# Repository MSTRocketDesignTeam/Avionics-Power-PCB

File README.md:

# Avionics-Power-PCB
KiCAD PCB files of rocket board designed to provide power and battery management functionalities

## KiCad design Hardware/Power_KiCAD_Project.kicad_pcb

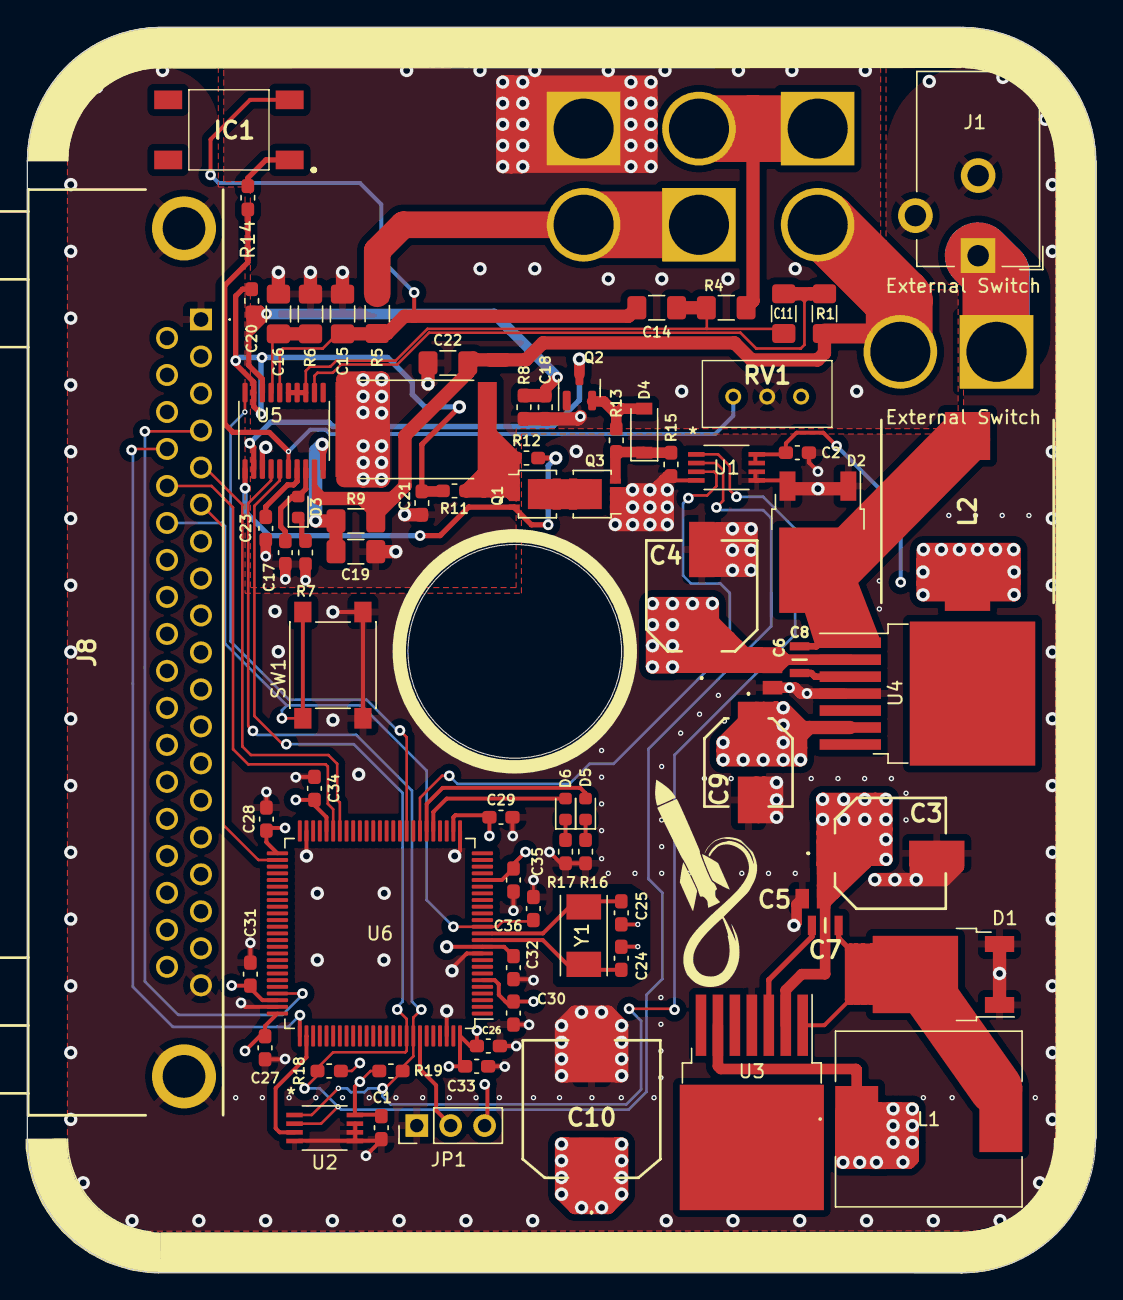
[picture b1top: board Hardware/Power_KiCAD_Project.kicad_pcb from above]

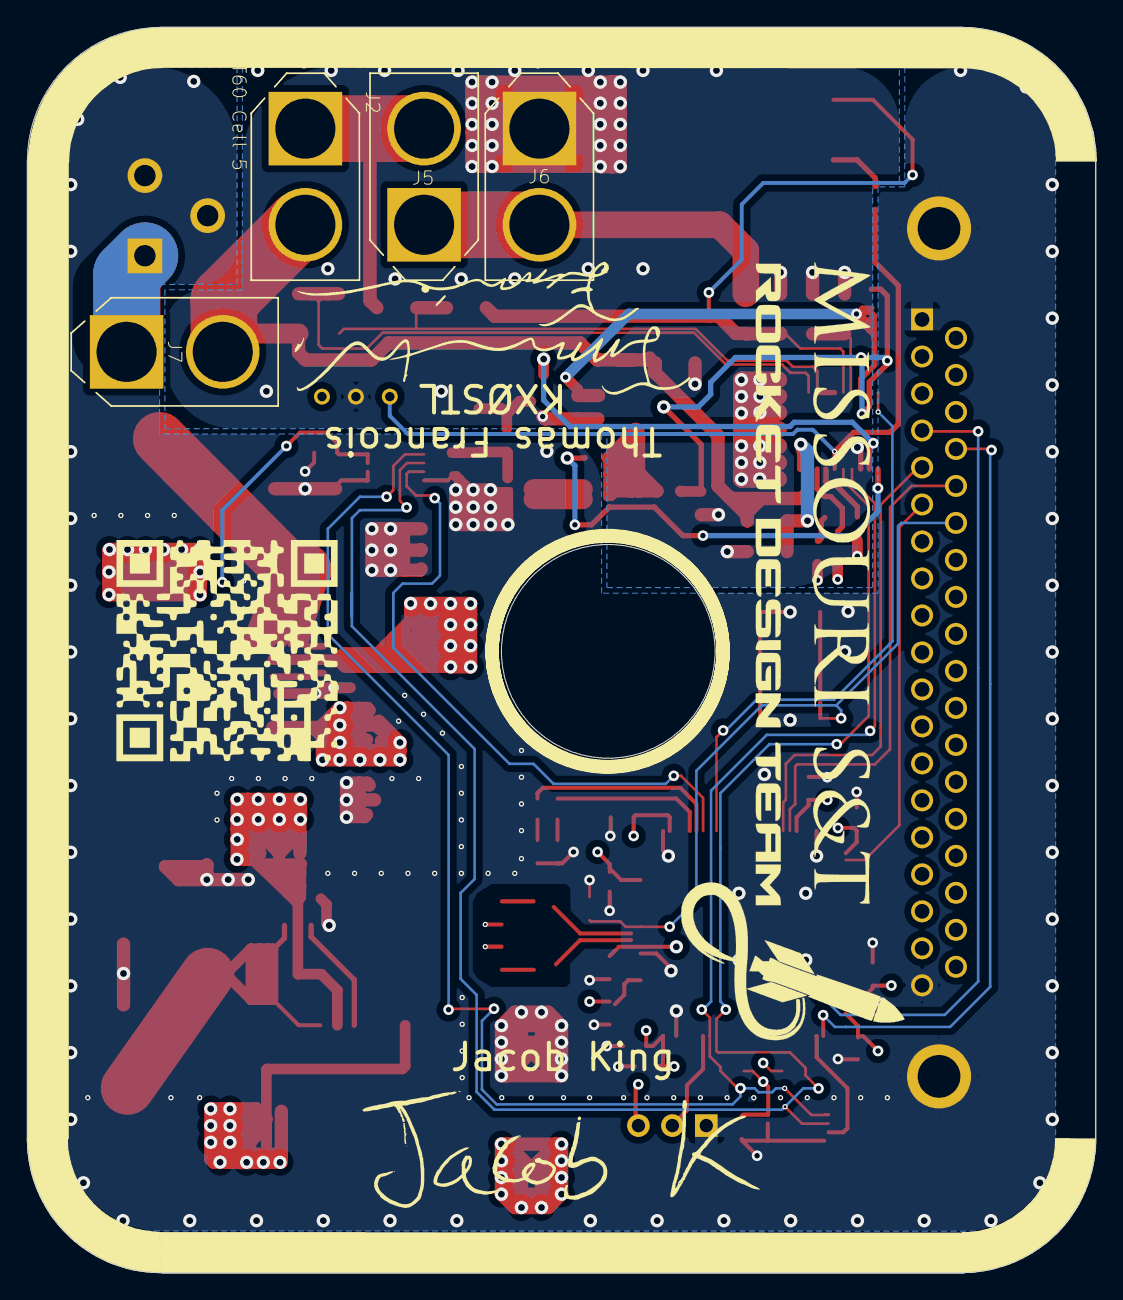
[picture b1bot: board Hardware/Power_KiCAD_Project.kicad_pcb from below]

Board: 4 copper layers, 80.0 x 93.2 mm, 79 parts (4 on the bottom side), 48 nets.

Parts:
C1, C2, C27, C28, C29, C30, C31, C32, C33, C34, C35, C36: 100nF; C_0603_1608Metric_Pad1.08x0.95mm_HandSolder
C3, C4: 35SVPF82M; 16SVPT560M
C5, C6: C0805C104M5RACTU; CAPC2012X88N
C7, C8: CGA4C2C0G1H103J060AA; CAPC2012X75N
C9: 6SVPC330M; 16SVF180M
C10: 16SVP330M; 16SVF1000M
C11, C14, C15, C16, C22: 1μF; C_1206_3216Metric_Pad1.42x1.75mm_HandSolder
C17: 4.7μF; C_0603_1608Metric_Pad1.08x0.95mm_HandSolder
C18, C20, C21: 0.1μF; R_0603_1608Metric_Pad1.05x0.95mm_HandSolder
C19: 10μF; C_1206_3216Metric_Pad1.42x1.75mm_HandSolder
C23: 1μF; C_0603_1608Metric_Pad1.08x0.95mm_HandSolder
C24, C25: 30pF; C_0603_1608Metric_Pad1.08x0.95mm_HandSolder
C26: 1uF; C_0603_1608Metric_Pad1.08x0.95mm_HandSolder
D1, D2: SBRD10200TR; TO-252-2
D3: LED; LED_0603_1608Metric
D4: 1N4148W-7-F; D_SOD-123
D5: GREEN; LED_0603_1608Metric
D6: RED; LED_0603_1608Metric
IC1: TL3301NF260QG
J1: Barrel_Jack_MountingPin; BarrelJack_CUI_PJ-102AH_Horizontal
J2: XT60 Cell 5; AMASS_XT60-M
J5: XT60 Cell 2; AMASS_XT60-M
J6: XT60 Cell 1; AMASS_XT60-M
J7: XT60 To External Switch; AMASS_XT60-M
J8: L717SDC37P1ACH4F
JP1: Debug Jumper; PinHeader_1x03_P2.54mm_Vertical
L1: IHLP5050FDER150M5A
L2: SRP1270-8R2M; INDPM137129X700N
Q1, Q3: PSMN2R6-40YS; LFPAK33
Q2: BSS84PH6327XTSA2; SOT-23
R1, R4, R5, R6, R9: 100Ω; R_1206_3216Metric_Pad1.42x1.75mm_HandSolder
R7, R16, R17: 1k5Ω; R_0603_1608Metric_Pad1.05x0.95mm_HandSolder
R8, R11: 100Ω; R_0603_1608Metric_Pad1.05x0.95mm_HandSolder
R10: CSS4527FT5L00
R12, R13, R15: 1MΩ; R_0603_1608Metric_Pad1.05x0.95mm_HandSolder
R14: 10kΩ; R_0603_1608Metric_Pad1.05x0.95mm_HandSolder
R18, R19: 4.7k; R_0603_1608Metric_Pad1.05x0.95mm_HandSolder
RV1: 10Ω to 2.2MΩ; T93YA5K10
SW1: MCU Reset; SW_SPST_PTS645
U1, U2: MIC184YMM-TR
U3: LM2678SX-5.0/NOPB; TO-263-7_TabPin8
U4: LM2678SX-3.3/NOPB; TO-263-7_TabPin8
U5: BQ76920PW; TSSOP-20_4.4x6.5mm_P0.65mm
U6: STM32L562VET; LQFP-100_14x14mm_P0.5mm
Y1: 32MHz; XTAL_ABM7-32.000MHZ-D2Y-T

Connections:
+3V3: C1.1, C2.1, C9.1, C26.1, C27.1, C28.1, C29.1, C30.1, C31.1, C32.1, C33.1, C34.1, C35.1, J8.2, J8.18, JP1.3 (B), L2.2, R18.2, R19.2, U1.7 (A0), U1.8 (VDD), U2.8 (VDD), U4.6 (FB), U6.6 (VBAT), U6.11 (VDD), U6.21 (VDDA), U6.27 (VDD), U6.46 (VDDSMPS), U6.51 (VDD), U6.73 (VDDUSB), U6.75 (VDD), U6.100 (VDD)
+5V: C10.1, J8.20, J8.37, L1.1, U3.6 (FB)
/BATT_ALERT: U5.20 (ALERT), U6.34 (PB2)
/Buck_Converters/V_IN: C3.1, C4.1, C5.1, C6.1, J1.1, J7.1 (-), U3.2 (VIN), U4.2 (VIN)
/DSUB-37_Bus/Alert_Active: J8.6, U6.52 (PB13)
/DSUB-37_Bus/Alert_scl: J8.5, U6.44 (PB10)
/DSUB-37_Bus/Alert_sda: J8.24, U6.45 (PB11)
/DSUB-37_Bus/NRST: C36.1, J8.25, SW1.1, U6.14 (NRST)
/DSUB-37_Bus/SWCLK: J8.23, U6.76 (PA14)
/DSUB-37_Bus/SWDIO: J8.4, U6.72 (PA13)
/I2C_SCL: R18.1, U1.2 (CLK), U2.2 (CLK), U5.5 (SCL), U6.92 (PB6)
/I2C_SDA: R19.1, U1.1 (DATA), U2.1 (DATA), U5.4 (SDA), U6.93 (PB7)
/LiPo Pack Monitor/VC0: C16.2, R6.2, U5.17 (VC0)
/LiPo Pack Monitor/VC1: C14.2, C15.1, IC1.3, R5.2, U5.16 (VC1)
/LiPo Pack Monitor/VC2: C11.2, C14.1, R4.2, U5.13 (VC4), U5.14 (VC3), U5.15 (VC2)
/LiPo Pack Monitor/VC5: C11.1, R1.2, U5.12 (VC5)
/PACK_M1: J5.1 (-), J6.2 (+), R5.1
/PACK_M2: J2.1 (-), J5.2 (+), R4.1
/PACK_M5: C22.2, J2.2 (+), J7.2 (+), R1.1, R9.1, U5.9 (REGSRC)
/TEMP_ALERT_1: U1.3 (INT), U6.32 (PB0)
/TEMP_ALERT_2: U2.3 (INT), U6.77 (PA15)
GND: C1.2, C2.2, C3.2, C4.2, C5.2, C6.2, C9.2, C10.2, C24.2, C25.2, C26.2, C27.2, C28.2, C29.2, C30.2, C31.2, C32.2, C33.2, C34.2, C35.2, C36.2, D1.1, D1.3, D2.1, D2.3, J1.2, J1.3 (MountPin), J8.1, J8.19, J8.MH1, J8.MH2, JP1.1 (A), Q3.1 (S), Q3.2 (S), Q3.3 (S), R15.2, R16.2, R17.2, SW1.2, U1.4 (GND), U1.5 (A2/T1), U1.6 (A1), U2.4 (GND), U2.5 (A2/T1), U2.6 (A1), U2.7 (A0), U3.4 (GND), U4.4 (GND), U6.10 (VSS), U6.26 (VSS), U6.49 (VSS), U6.74 (VSS), U6.98 (VSS)
GNDREF: C15.2, C16.1, C17.1, C18.2, C19.1, C21.1, C22.1, C23.1, J6.1 (-), Q2.1 (G), R6.1, R7.2, R8.2, R10.1, RV1.2, U5.3 (VSS)
unnamed: C7.1, U3.3 (CB)
unnamed: C7.2, D1.2, L1.2, U3.1 (SWO)
unnamed: C8.1, U4.3 (CB)
unnamed: C8.2, D2.2, L2.1, U4.1 (SWO)
unnamed: C17.2, D3.2 (A), U5.8 (REGOUT)
unnamed: C18.1, C20.2, R8.1, U5.18 (SRP)
unnamed: C19.2, R9.2, U5.10 (BAT)
unnamed: C20.1, C21.2, R11.1, U5.19 (SRN)
unnamed: C23.2, U5.7 (CAP1)
unnamed: C24.1, U6.12 (PH0), Y1.1
unnamed: C25.1, U6.13 (PH1), Y1.2
unnamed: D3.1 (K), R7.1
unnamed: D4.1 (K), Q3.4 (G), R13.1, R15.1
unnamed: D4.2 (A), Q2.2 (S), R13.2
unnamed: D5.1 (K), R16.1
unnamed: D5.2 (A), U6.31 (PA7)
unnamed: D6.1 (K), R17.1
unnamed: D6.2 (A), U6.30 (PA6)
unnamed: IC1.1, R14.2
unnamed: JP1.2 (C), U6.94 (PH3)
unnamed: Q1.1 (S), Q1.2 (S), Q1.3 (S), R10.2, R11.2, R12.2
unnamed: Q1.4 (G), R12.1, U5.1 (DSG)
unnamed: Q1.5 (D), Q3.5 (D)
unnamed: Q2.3 (D), U5.2 (CHG)
unnamed: R14.1, RV1.1, U5.6 (TS1)

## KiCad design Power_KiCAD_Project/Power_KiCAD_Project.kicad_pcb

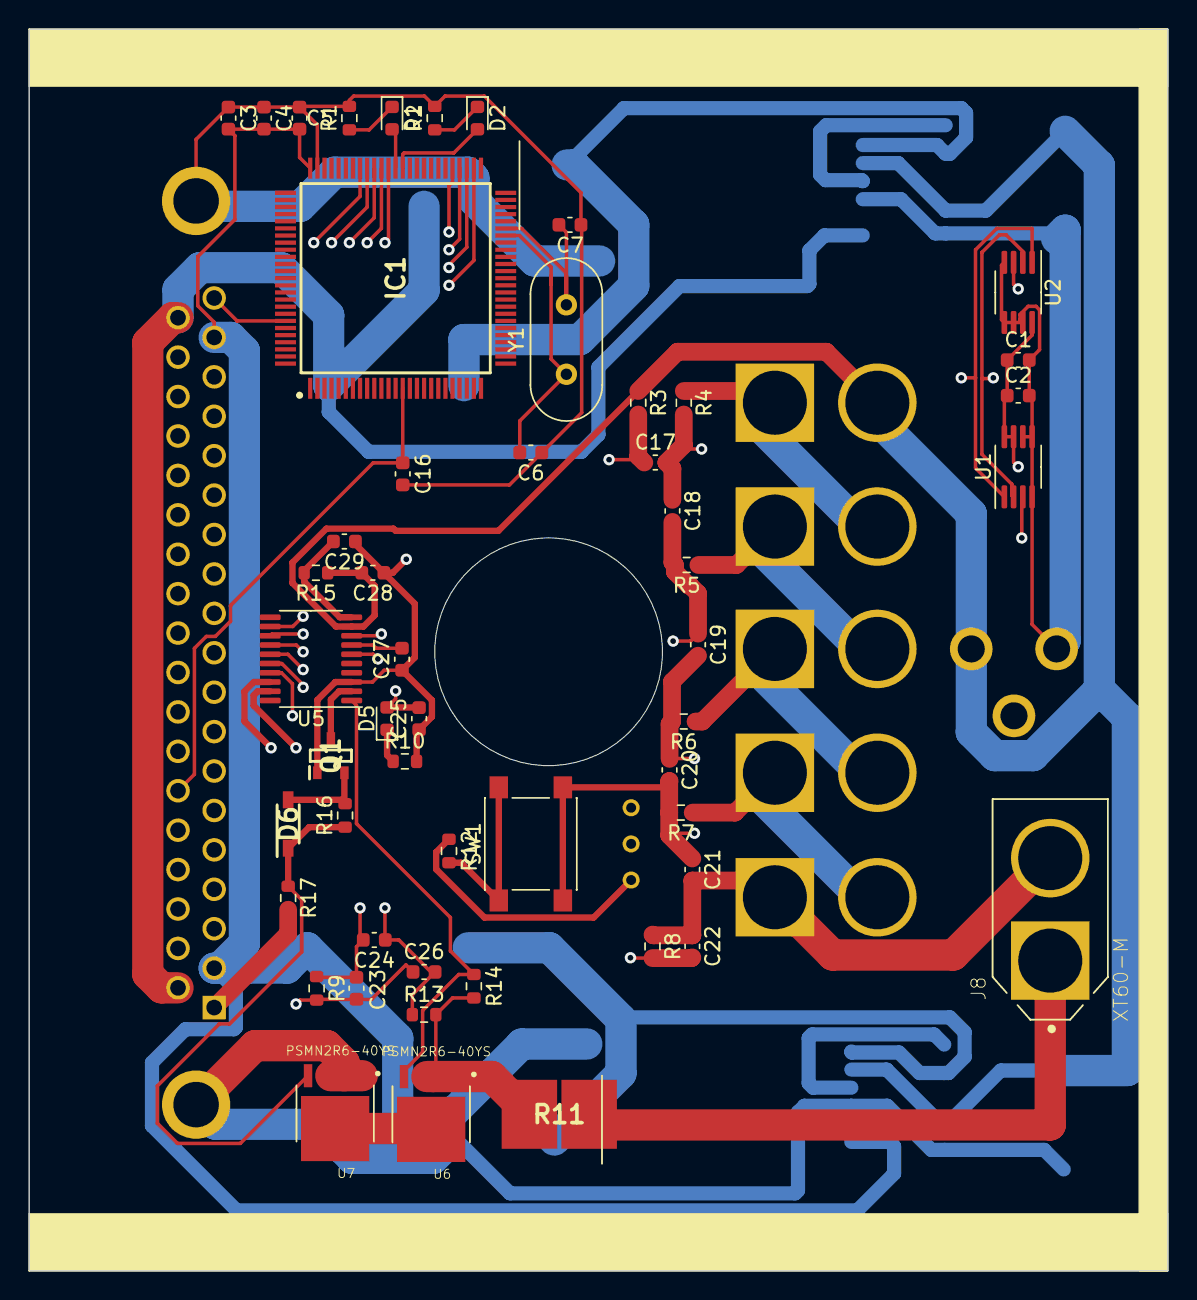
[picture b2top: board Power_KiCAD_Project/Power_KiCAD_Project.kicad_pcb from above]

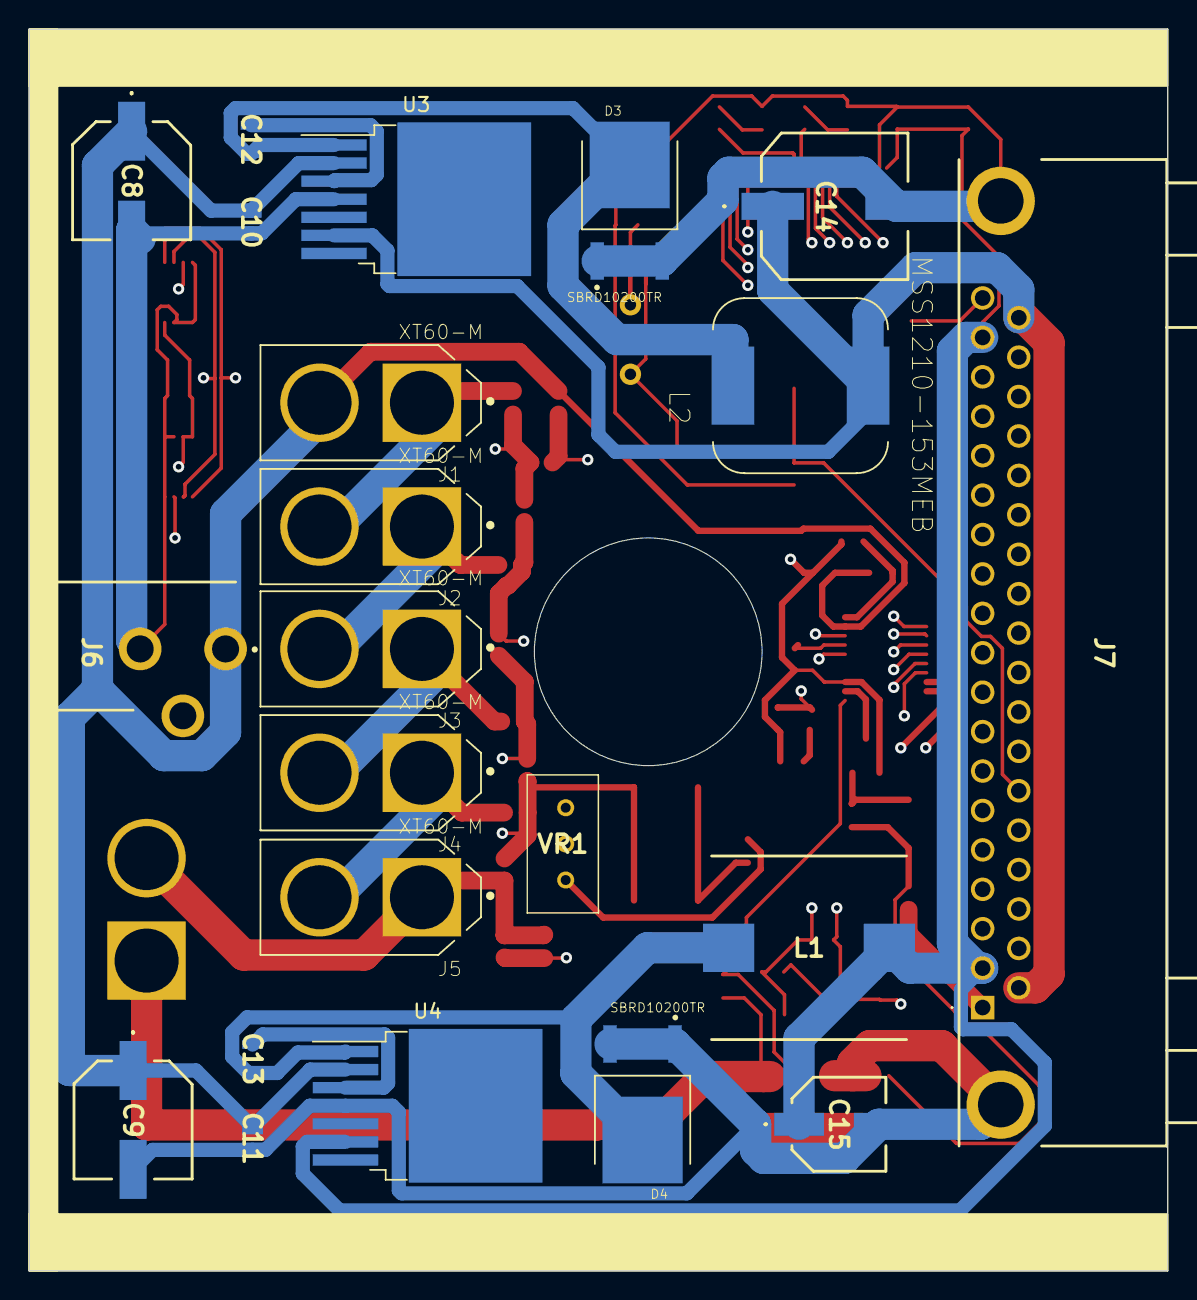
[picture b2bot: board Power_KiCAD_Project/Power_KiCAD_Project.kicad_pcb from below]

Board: 4 copper layers, 80.0 x 87.2 mm, 74 parts (22 on the bottom side), 49 nets.

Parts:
C1, C2, C4, C5, C16: 100nF; C_0603_1608Metric
C3: 1uF; C_0603_1608Metric
C6, C7: 30pF; C_0603_1608Metric
C8, C9: 35SVPF82M; 16SVPT560M
C10, C11: C0805C104M5RACTU; CAPC2012X88N
C12, C13: CGA4C2C0G1H103J060AA; CAPC2012X75N
C14: 16SVP330M; 16SVF1000M
C15: 6SVPC330M; 16SVF180M
C17, C18, C19, C20, C21, C22, C27, C28: 1μF; C_0603_1608Metric
C23, C24, C26: 0.1μF; C_0603_1608Metric
C25: 4.7μF; C_0603_1608Metric
C29: 10μF; C_0603_1608Metric
D1: GREEN; LED_0603_1608Metric
D2: RED; LED_0603_1608Metric
D3, D4: SBRD10200TR; DPAK228P1005X240-4N
D5: LED; LED_0603_1608Metric
D6: 1N4148W-7-F; SOD3716X145N
IC1: STM32L562VET6Q; QFP50P1600X1600X160-100N
J1, J2, J3, J4, J5, J8: XT60-M; AMASS_XT60-M
J6: PJ-102AH
J7: L717SDC37P1ACH4F
L1: SRP1270-8R2M; INDPM137129X700N
L2: MSS1210-153MEB; IND_MSS1210-153MEB
Q1: BSS84PH6327XTSA2; SOT95P240X110-3N
R1, R2, R10: 1k5Ω; R_0603_1608Metric
R3, R4, R5, R6, R7, R8, R9, R13, R15: 100Ω; R_0603_1608Metric
R11: WSHP28185L000FEA; RESC7146X175N
R12: 10kΩ; R_0603_1608Metric
R14, R16, R17: 1MΩ; R_0603_1608Metric
SW1: Reboot; SW_Push_1P1T_NO_6x6mm_H9.5mm
U1, U2: MCP9808_MSOP; MSOP-8_3x3mm_P0.65mm
U3: LM2678SX-5.0/NOPB; TO-263-7_TabPin8
U4: LM2678SX-3.3/NOPB; TO-263-7_TabPin8
U5: BQ76920PW; TSSOP-20_4.4x6.5mm_P0.65mm
U6, U7: PSMN2R6-40YS; TO127P600X120-5N
VR1: T93YA103KT20; T93YA5K10
Y1: Crystal; Crystal_HC49-4H_Vertical

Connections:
+3V3: C1.1, C2.1, C3.2, C4.2, C5.2, C15.1, IC1.75, J7.2, J7.18, L1.2, U1.7, U1.8, U2.8, U4.6
+5V: C14.1, J7.20, J7.37, L2.2, U3.6
/Alert_active: IC1.68, J7.6
/Alert_scl: IC1.66, J7.5
/Alert_sda: IC1.67, J7.24
/I2C_SCL: IC1.52, U1.2, U2.2
/I2C_SDA: IC1.53, U1.1, U2.1
/LiPo Pack Monitor/BAT: C29.2, R15.2, U5.10
/LiPo Pack Monitor/SRN: C24.1, C26.2, R13.1, U5.19
/LiPo Pack Monitor/SRP: C23.1, C24.2, R9.1, U5.18
/LiPo Pack Monitor/TS1: R12.1, U5.6, VR1.1
/LiPo Pack Monitor/VC0: C22.2, R8.2, U5.17
/LiPo Pack Monitor/VC1: C20.2, C21.1, R7.2, SW1.2, U5.16
/LiPo Pack Monitor/VC2: C19.2, C20.1, R6.2, U5.15
/LiPo Pack Monitor/VC3: C18.2, C19.1, R5.2, U5.14
/LiPo Pack Monitor/VC4: C17.2, C18.1, R4.2, U5.13
/LiPo Pack Monitor/VC5: C17.1, R3.2, U5.12
/NRST: C16.1, IC1.14, J7.25
/PACK_M1: J4.1, J5.2, R7.1
/PACK_M2: J3.1, J4.2, R6.1
/PACK_M3: J2.1, J3.2, R5.1
/PACK_M4: J1.1, J2.2, R4.1
/PACK_M5: C8.1, C9.1, C10.1, C11.1, C28.2, J1.2, J6.1, R3.1, R15.1, U3.2, U4.2, U5.9
/Pack-: C1.2, C2.2, C3.1, C4.1, C5.1, C6.1, C7.1, C8.2, C9.2, C10.2, C11.2, C14.2, C15.2, C16.2, D3.1, D3.3, D4.1, D4.3, IC1.74, IC1.94, J6.2, J7.1, J7.19, J7.MH1, J7.MH2, R1.2, R2.2, R17.2, U1.4, U1.5, U1.6, U2.4, U2.5, U2.6, U2.7, U3.4, U4.4, U7.1, U7.2, U7.3
/SWCLK: IC1.55, J7.23
/SWDIO: IC1.54, J7.4
/TEMP_ALERT_1: IC1.64, U1.3
/TEMP_ALERT_2: IC1.65, U2.3
GND: C21.2, C22.1, C23.2, C25.1, C26.1, C27.1, C28.1, C29.1, J5.1, J8.1, J8.2, Q1.1, R8.1, R9.2, R10.2, R11.1, U5.3, VR1.2, VR1.3
unnamed: C6.2, IC1.44, Y1.1
unnamed: C7.2, IC1.45, Y1.2
unnamed: C12.1, U3.3
unnamed: C12.2, D3.2, L2.1, U3.1
unnamed: C13.1, U4.3
unnamed: C13.2, D4.2, L1.1, U4.1
unnamed: C25.2, D5.2, U5.8
unnamed: C27.2, U5.7
unnamed: D1.1, R1.1
unnamed: D1.2, IC1.63
unnamed: D2.1, R2.1
unnamed: D2.2, IC1.62
unnamed: D5.1, R10.1
unnamed: D6.1, R16.1, R17.1, U7.4
unnamed: D6.2, Q1.2, R16.2
unnamed: Q1.3, U5.2
unnamed: R11.2, R13.2, R14.2, U6.1, U6.2, U6.3
unnamed: R12.2, SW1.1
unnamed: R14.1, U5.1, U6.4
unnamed: U6.5, U7.5

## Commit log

2021-10-01 Schematic v1.0.0
    Creation of KiCAD project file, initial draft of PCB schematic file, components chosen as a starting point and will likely be altered in future revisions.
2021-10-01 Schematic v.1.0.1
    Added XT60 and LiPo Pack Monitor Connectors to schematic file.
    Added Temperature Sensor Chips to I2C bus.
    Still need to add LiPo Charge Controller chip and DC barrel jack.
    Might want to pick slightly larger MCU for 2nd I2C bus, right now sensors are on the main system bus.
2021-10-01 Schematic v1.0.2
    Added Pack+/- tags to LiPo Monitor
2021-10-06 Schematic v1.0.3
    Compartmentalized the root page.
2021-10-06 Github Test
    This is a test
2021-10-13 Changed labels from global to local
2021-11-03 Updated With c=Connections
    Added connections for power and for card slots
2021-11-24 Changes to bus
    bus was changed
2021-11-29 Added main Buck Converters & Question about grounding
    I think that the BMS Ground needs to be separated from the main board ground since the BMS uses low side switching to protect the batteries. Like it is currently setup, the current can bypass the swi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
2021-11-29 Part Naming Correction
2021-12-01 added components
    added a few components and the correct numbers
2021-12-02 pcb finished
    pcb is done. 3am kicad be like
2021-12-02 Changes to PCB
    Bunch of changes to layout with components on the other side
2021-12-03 updated pcb
    more updates because stuff was a bit too far away from their connected components
2021-12-03 pcb update
    More changes to pcb layout
2021-12-04 Changes to PCB
    re did the pcb and added a "switch"
    basically its just an xt60 connector in series with the other ones that needs to be shorted for the board to get power
2021-12-05 PCB changes
    did some changes to the PCB to make sure that everything is fully isolated.
2021-12-06 Reformatted repo
2021-12-06 Added files from global
    Added and appended files from my global libraries
2021-12-06 Updated symbols
    Final update to the symbols from my global
2021-12-06 FIxed board
    issues with the board after the merge have been fixed
2021-12-10 Size change on pcb
    Pcb size was changed to add 3mm on the top and bottom. libraries were also updated
2021-12-21 Replaced passive component footprints with handsolder variants
    I think the component sheet for the MCU STM32L152VET6Q is incorrect. Will investigate.
2021-12-21 Component sheets added
    Component sheets were added from the telemetry board to match across all boards
2021-12-21 Rearranged LiPo Monitor component sheet
    - Added XT60 connector for external switch connection
    - Updated a few component symbols to be the default ones
    - Replaced label "ground" with the GNDREF symbol
    - LiPo Pack Monitor I2C and Alert Lines still need to be added
2021-12-21 Fixed ground symbols in component sheets, corrected MCU sheet
2021-12-21 Updated component footprints, moved to RDT_Custom_Footprints library
2021-12-21 Updated Buck Converter component sheet
2021-12-21 Cleaned up main schematic page, connected barrel jack ground pin to GND
    Is this ok? The Barrel Jack is like this right now:
    Pin -> Pack+
    Barrel -> GNDREF
    Mounting Pin -> GND
2021-12-21 Reset annotations, changed SPST switch footprint
2021-12-22 Added 3d step models to every component
2021-12-22 Progress made to the battery section
2021-12-22 Routed battery side of pcb
    GNDREF has its own island on the inner copper layer, separate from the rest of the components which will get a normal GND inner copper layer
2021-12-22 Increased spacing between XT60 connectors
2021-12-22 Adjusted GNDREF and GND copper zones
2021-12-22 Adjusted a few references
2021-12-27 Routed 3v3 and 5v buck converters
    Switched to working on my laptop so some of the component references might be messed up for a bit
2021-12-27 Initial routing and placement of power inductors
2021-12-27 Routed all 3v3 and 5v traces to dsub
2021-12-27 Placed MCU and routed crystal ground plane
2021-12-28 Placed mcu and filter caps
2021-12-28 Added I2C lines to lipo monitor schematic page
2021-12-28 Routed I2C lines between temp sensors, lipo monitor, and mcu
2021-12-28 Misc trace routings
2021-12-28 Completed all connections for GNDREF side of board
    Having C18 and C21 connected to GNDREF feels weird because it's bypassing the connector for the external switch. Will check this later
2021-12-28 Routed data busses from MCU to DB37
2021-12-28 All components and connections are made
2021-12-28 Fixed issues with copper fill clearances
2021-12-28 Adjusted silk screen labels
2021-12-29 Adjusted power trace geometries
2021-12-29 Adjusted position of vias to maximize clearance
2021-12-29 Adjustments to inner copper pours
2021-12-29 More adjustments to inner copper pours
2021-12-29 Even more copper pour adjustments
2022-01-12 Moved external switch connector to pack+, added missing no connection flags
    This change renders the current PCB layout defunct, next commits will be redesigns of the layout.
2022-01-12 Added design rules for JLCPCB
2022-01-13 Routed GNDREF side of board
    Correcting keepout silkscreen added 3mm to top and bottom, much appreciated!
2022-01-13 Routed 3v3 and 5v buck converters
2022-01-13 Routed most internal power/ground planes
2022-01-13 Attempting to add ground vias to help with emi
2022-01-14 More adjustments of internal planes
2022-01-14 Routed all connections and placed all components
    MCU crystal still needs a ground peninsula
2022-01-14 Added ground peninsula for MCU crystal
2022-01-14 Adjustments to silk screen
2022-01-15 Changed DB37 connector to correct 3D model
2022-01-18 added qr code
    qr code was added and corners were rounded
2022-01-25 Added signatures to silkscreen
2022-01-30 updated parts
    parts were switched out due to lack of stock to ones with stock
2022-01-31 Corrected 3D models
2022-02-01 Smoothed Jacob's madness
2022-02-01 Power resistor now fits on top side of board
2022-02-01 Corrected clock crystal on MCU
2022-02-04 Separated I2C Lines
    For better EMI/EMC mitigation.
2022-02-05 Added bootloader pins, adjusted lipo monitor and mcu buttons
2022-02-05 rearranged silkscreen labels
2022-02-07 Added QR Code to Silkscreen
2022-02-07 Removed wrong stitching via
2022-02-08 Aligned board to grid, rounded copper pours, adjusted stitching vias around edges
2022-02-08 Added some stitching vias to GNDREF end of board
2022-02-08 Replaced .wrl models with .step
2022-02-14 Moved XT60 connectors to back side, adjusted silkscreen, added polarity labels
2022-02-14 Moved external switch XT60 to back side
2022-02-19 Progress 1 to small board
    Changed components around,deleted xt60s
2022-02-19 Updated hole Location
    hole was moved to the left 2mm and components that were in the way were also moved over. this is to give more tolerance
2022-04-29 generated gerbs
    gerbers were generated for pcb manufacturing
2022-04-29 Gerbers In ZIP
    files were zipped and deleted from main
2022-05-09 Test
2022-05-09 Removed LiPo connectors 4 and 5, flipped connectors
2022-10-16 Create TEST.txt
    testpush
2022-10-16 Delete TEST.txt
    testdelete

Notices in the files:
parts and their libraries:
Copyright 2021 Accelerated Designs. All rights reserved.
